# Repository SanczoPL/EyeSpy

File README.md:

# EyeSpy
App na Raspberry pi2/3 - linefollowing robot

# OpenCV-PC-example
PC program show 
# PCB
PCB 
# src
source
# config.json
config file
# CMakeLists.txt
cmake file

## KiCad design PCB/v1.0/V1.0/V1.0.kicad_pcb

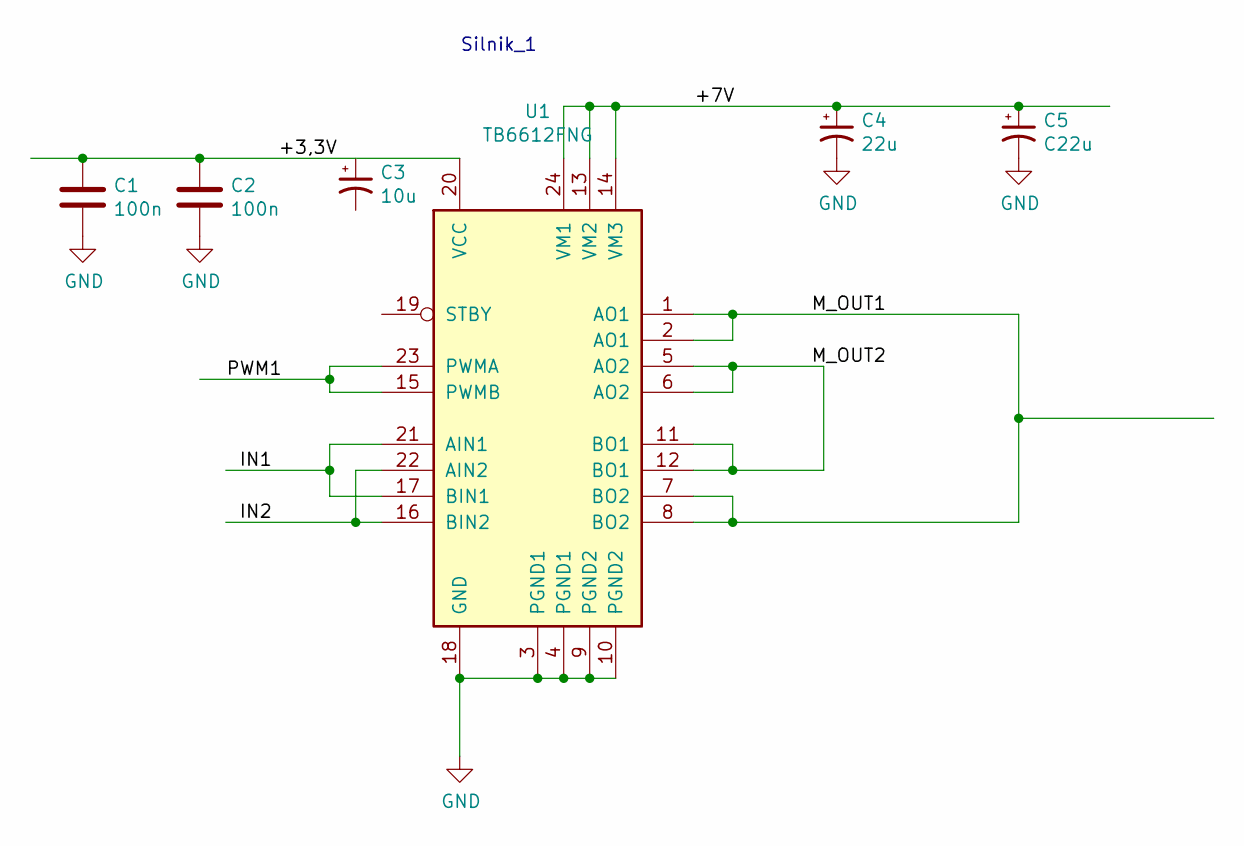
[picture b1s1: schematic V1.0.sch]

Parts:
C1, C2: 100n; C_0805_2012Metric_Pad1.15x1.40mm_HandSolder
C3: 10u; CP_Elec_5x3
C4: 22u; CP_Elec_5x3
C5: C22u; CP_Elec_5x3
U1: TB6612FNG; SSOP-24_5.3x8.2mm_P0.65mm

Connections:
/+3,3V: C1.1, C2.1, U1.20 (VCC)
/+7V: C4.1, C5.1, U1.13 (VM2), U1.14 (VM3), U1.24 (VM1)
/IN1: U1.17 (BIN1), U1.21 (AIN1)
/IN2: U1.16 (BIN2), U1.22 (AIN2)
/M_OUT1: U1.1 (AO1), U1.2 (AO1), U1.7 (BO2), U1.8 (BO2)
/M_OUT2: U1.5 (AO2), U1.6 (AO2), U1.11 (BO1), U1.12 (BO1)
/PWM1: U1.15 (PWMB), U1.23 (PWMA)
GND: C1.2, C2.2, C4.2, C5.2, U1.3 (PGND1), U1.4 (PGND1), U1.9 (PGND2), U1.10 (PGND2), U1.18 (GND)

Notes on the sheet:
Silnik_1

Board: 2 copper layers, 6 parts (0 on the bottom side), 8 nets, no tracks yet.
